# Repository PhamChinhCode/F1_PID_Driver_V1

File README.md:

# F1_PID_Driver_V1

Mạch driver động cơ DC chổi than có điều khiển PID, thiết kế bằng **KiCad**.
Cầu H 4 × N-MOSFET, gate driver IR2184 bootstrap, cách ly quang giữa MCU và phần công suất, vi điều khiển **STM32F103C8** đọc encoder và chạy vòng PID vị trí/tốc độ.

| Mặt trên | Mặt dưới |
|---|---|
|  |  |

## Thông số chính

| Mục | Giá trị |
|---|---|
| Kích thước PCB | 45 × 65 mm, 2 lớp, đồng 1 oz |
| Điện áp động cơ (VM) | ~18 – 35 V (giới hạn bởi L7815 và tụ 50 V) |
| Dòng liên tục thực tế | ~8 – 10 A (giới hạn bởi đồng 1 oz và terminal) |
| MOSFET | 4 × IRFS4321 (TO-263, 150 V) |
| Gate driver | 2 × IR2184 (half-bridge, dead-time nội) |
| Cách ly | HCPL-0630 (2 kênh) cho PWMA/PWMB |
| MCU | STM32F103C8T6, thạch anh ngoài, SWD |
| Logic 3.3 V | AMS1117-3.3, cấp 5 V từ các cổng JST |

## Sơ đồ khối

```
 VM ──F1──┬── Cầu H (Q1–Q4 IRFS4321) ── M+ / M−
          │        ▲            ▲
          │     IR2184 (U1)  IR2184 (U2)
          │        ▲            ▲
          ├─ L7815 → +15VP → AMS1117-5.0 → +5VP
          │        │  PWMA        │ PWMB
          │   ─────┴── HCPL-0630 ─┴─────   (cách ly COM ↔ GND)
          │                ▲
 +5V (JST) → AMS1117-3.3 → STM32F103C8
                           ├─ TIM2 encoder  (PA0/PA1, qua 74x14)
                           ├─ STEP/DIR      (PA6/PA7, qua 74x14)
                           ├─ ADC biến trở  (PA3)
                           ├─ UART1 (PA9/PA10), I2C2 (PB10/PB11)
                           └─ Địa chỉ node  JP1–JP4 (PB12–PB15)
```

## Mapping chân MCU

| Chức năng | Chân | Ngoại vi |
|---|---|---|
| Encoder A/B | PA0 / PA1 | TIM2 encoder mode |
| PULSE (step) | PA6 | TIM3_CH1 |
| DIR | PA7 | GPIO |
| ADIR | PA4 | GPIO |
| Biến trở (analog) | PA3 | ADC1_IN3 |
| PWMA / PWMB | PB6 / PB7 | TIM4_CH1 / CH2 → opto → IR2184 |
| UART | PA9 / PA10 | USART1 |
| I2C | PB10 / PB11 | I2C2 (pull-up 4k7) |
| Địa chỉ node | PB12 – PB15 | Solder jumper xuống GND (ID 0–15) |
| Nạp/debug | PA13 / PA14 | SWD |

> Lưu ý firmware: 74x14 là Schmitt **đảo**, nên tín hiệu DIR/encoder/step bị đảo. Do dùng bootstrap, duty high-side không được giữ 100 % lâu (~95–98 % tối đa).

## Cấu trúc thư mục

| Đường dẫn | Nội dung |
|---|---|
| `F1_PID_Driver_V1.kicad_pro` | Project KiCad |
| `F1_PID_Driver_V1.kicad_sch` | Schematic |
| `F1_PID_Driver_V1.kicad_pcb` | PCB layout |
| `F1_PID_Driver_V1.pdf` | Schematic xuất PDF |
| `bom/ibom.html` | Interactive BOM (mở bằng trình duyệt) |
| `gerber_to_order/` | Gerber cho JLCPCB, PCBWay, Elecrow, FusionPCB… |
| `REVIEW_F1_PID_Driver_V1.md` | Báo cáo review thiết kế (ERC/DRC, lỗi, đề xuất V2) |

## Trạng thái

⚠️ **Bản V1 còn lỗi đã biết** — xem chi tiết trong [REVIEW_F1_PID_Driver_V1.md](REVIEW_F1_PID_Driver_V1.md). Những điểm quan trọng nhất:

- Zener D10 ở ngõ ADC lắp ngược chiều.
- AMS1117-5.0 nhận 15 V (sát/vượt abs-max).
- Thiếu tụ 10 µF ngõ ra LDO, dòng LED opto thấp (R8/R9 330 Ω).
- nSD luôn kéo lên, MCU không tắt được cầu H.
- Gerber trong `gerber_to_order/` (18/06/2026) **cũ hơn** file PCB (04/08/2026) — cần refill zone, chạy DRC và xuất lại trước khi đặt mạch.

Checklist sửa cho V1.1 nằm ở mục 6 của file review.

## Mở dự án

1. Cài [KiCad](https://www.kicad.org/) **10** trở lên (file được lưu bằng KiCad 10, bản cũ hơn không mở được).
2. Mở `F1_PID_Driver_V1.kicad_pro`.
3. Nếu thiếu thư viện/footprint, kiểm tra *Preferences → Manage Symbol/Footprint Libraries*.

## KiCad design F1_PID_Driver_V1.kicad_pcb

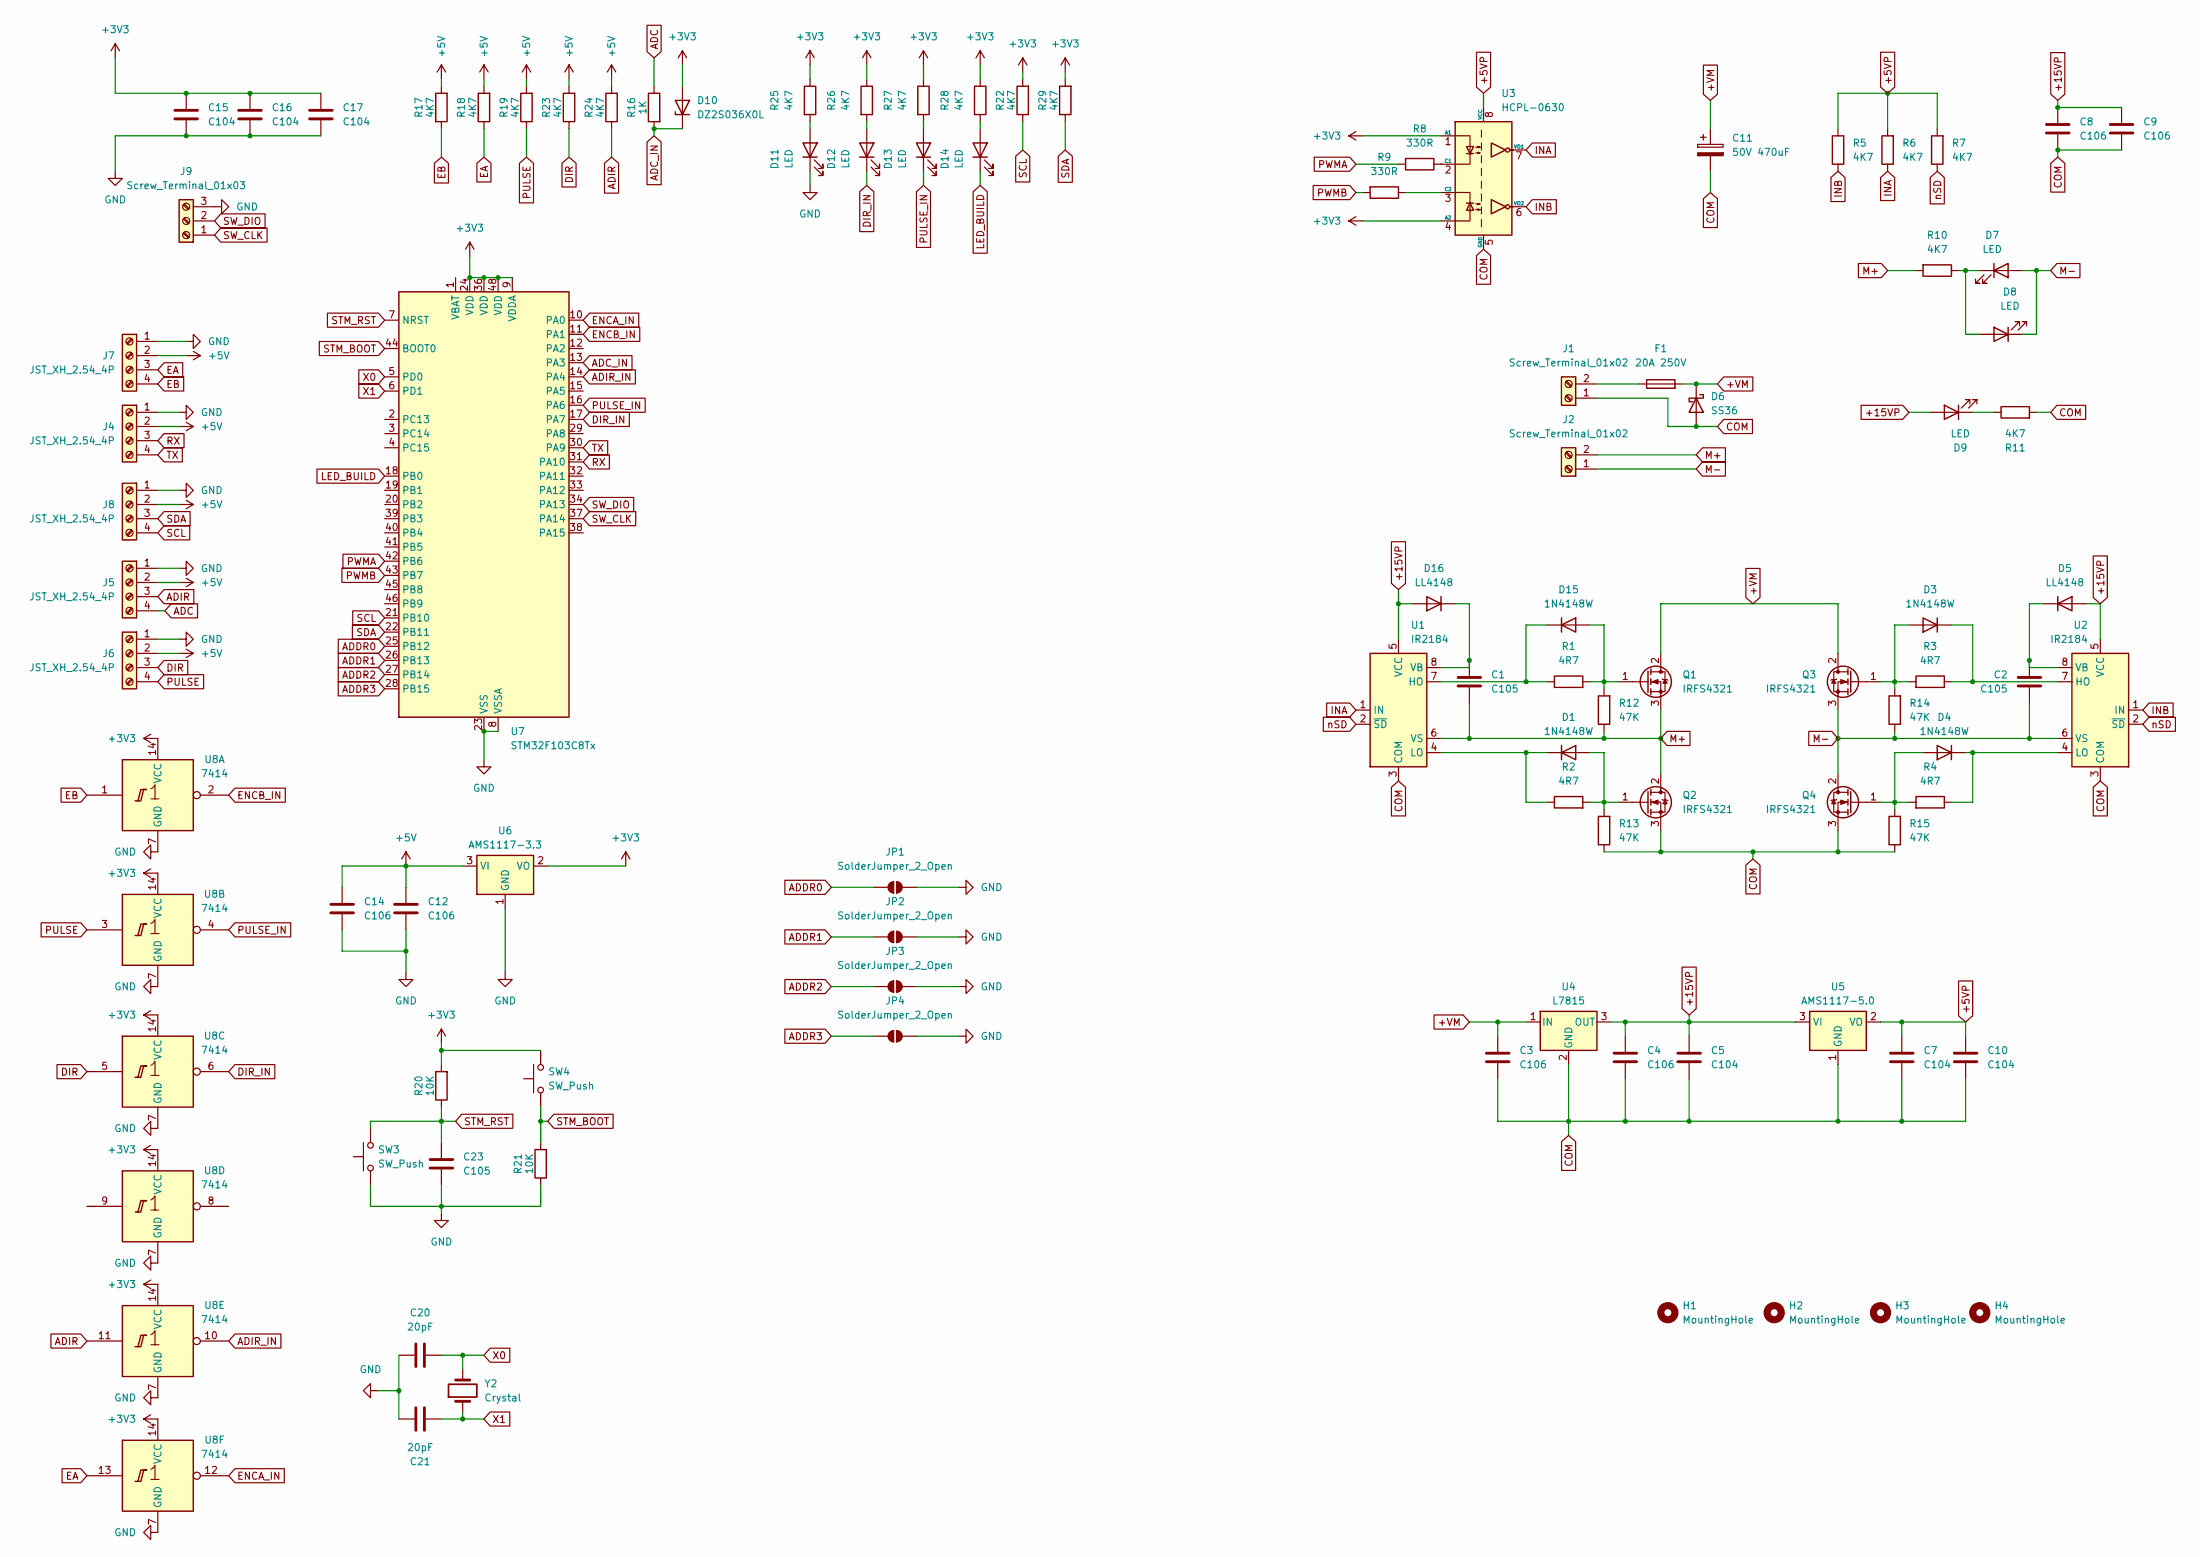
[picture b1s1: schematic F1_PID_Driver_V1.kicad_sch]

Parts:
C1, C2, C23: C105; C_0805_2012Metric
C3, C4, C8, C9: C106; C_1206_3216Metric
C5, C7, C10, C15, C16, C17: C104; C_0805_2012Metric
C11: 50V 470uF; CP_Radial_D10.0mm_P3.50mm
C12, C14: C106; C_0805_2012Metric
C20, C21: 20pF; C_0805_2012Metric
D1, D3, D4, D15: 1N4148W; D_SOD-123
D5, D16: LL4148; D_MiniMELF
D6: SS36; D_SMA
D7, D8, D9, D11, D12, D13, D14: LED; LED_0603_1608Metric
D10: DZ2S036X0L; D_SOD-123F
F1: 20A 250V; Fuseholder_Clip-5x20mm_Keystone_3512_Inline_P23.62x7.27mm_D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
H1, H2, H3, H4: MountingHole; MountingHole_3.2mm_M3_Pad_Via
J1, J2: Screw_Terminal_01x02; TerminalBlock_Phoenix_MKDS-1,5-2-5.08_1x02_P5.08mm_Horizont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
J4, J5, J6, J7, J8: JST_XH_2.54_4P; XH2.54-4P
J9: Screw_Terminal_01x03; JST_PH_B3B-PH-SM4-TB_1x03-1MP_P2.00mm_Vertical
JP1, JP2, JP3, JP4: SolderJumper_2_Open; SolderJumper-2_P1.3mm_Open_RoundedPad1.0x1.5mm
Q1, Q2, Q3, Q4: IRFS4321; TO-263-2
R1, R2, R3, R4: 4R7; R_0805_2012Metric
R5, R6, R7, R10, R11, R17, R18, R19, R22, R23, R24, R25, R26, R27, R28, R29: 4K7; R_0603_1608Metric
R8, R9: 330R; R_0603_1608Metric
R12, R13, R14, R15: 47K; R_0603_1608Metric
R16: 1K; R_0603_1608Metric
R20, R21: 10K; R_0603_1608Metric
SW3, SW4: SW_Push; SW_SPST_TS-1088-xR025
U1, U2: IR2184; SOIC-8_3.9x4.9mm_P1.27mm
U3: HCPL-0630; SOIC-8_3.9x4.9mm_P1.27mm
U4: L7815; TO-252-2
U5: AMS1117-5.0; SOT-223-3_TabPin2
U6: AMS1117-3.3; SOT-223-3_TabPin2
U7: STM32F103C8Tx; LQFP-48_7x7mm_P0.5mm
U8: 7414; SOIC-14_3.9x8.7mm_P1.27mm
Y2: Crystal; Crystal_HC49-4H_Vertical

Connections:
+3V3: C15.1, C16.1, C17.1, D10.2 (A), R20.2, R22.2, R25.1, R26.1, R27.1, R28.1, R29.2, SW4.2, U3.1 (A1), U3.4 (A2), U6.2 (VO), U7.9 (VDDA), U7.24 (VDD), U7.36 (VDD), U7.48 (VDD), U8.14 (VCC)
+5V: C12.1, C14.1, J4.2, J5.2, J6.2, J7.2, J8.2, R17.2, R18.2, R19.2, R23.2, R24.2, U6.3 (VI)
+5VP: C7.1, C10.1, R5.2, R6.2, R7.2, U3.8 (VCC), U5.2 (VO)
+15VP: C4.1, C5.1, C8.1, C9.1, D5.2 (A), D9.2 (A), D16.2 (A), U1.5 (VCC), U2.5 (VCC), U4.3 (OUT), U5.3 (VI)
+VM: C3.1, C11.1, D6.1 (K), F1.2, Q1.2 (D), Q3.2 (D), U4.1 (IN)
ADC: J5.4, R16.1
ADC_IN: D10.1 (K), R16.2, U7.13 (PA3)
ADDR0: JP1.1 (A), U7.25 (PB12)
ADDR1: JP2.1 (A), U7.26 (PB13)
ADDR2: JP3.1 (A), U7.27 (PB14)
ADDR3: JP4.1 (A), U7.28 (PB15)
ADIR: J5.3, R24.1, U8.11
ADIR_IN: U7.14 (PA4), U8.10
COM: C3.2, C4.2, C5.2, C7.2, C8.2, C9.2, C10.2, C11.2, D6.2 (A), J1.1, Q2.3 (S), Q4.3 (S), R11.2, R13.1, R15.1, U1.3 (COM), U2.3 (COM), U3.5 (GND), U4.2 (GND), U5.1 (GND)
DIR: J6.3, R23.1, U8.5
DIR_IN: D12.1 (K), U7.17 (PA7), U8.6
EA: J7.3, R18.1, U8.13
EB: J7.4, R17.1, U8.1
ENCA_IN: U7.10 (PA0), U8.12
ENCB_IN: U7.11 (PA1), U8.2
GND: C12.2, C14.2, C15.2, C16.2, C17.2, C20.1, C21.1, C23.2, D11.1 (K), J4.1, J5.1, J6.1, J7.1, J8.1, J9.3, JP1.2 (B), JP2.2 (B), JP3.2 (B), JP4.2 (B), R21.1, SW3.1, U6.1 (GND), U7.8 (VSSA), U7.23 (VSS), U7.35 (VSS), U7.47 (VSS), U8.7 (GND)
INA: R6.1, U1.1 (IN), U3.7 (VO1)
INB: R5.1, U2.1 (IN), U3.6 (VO2)
LED_BUILD: D14.1 (K), U7.18 (PB0)
M+: C1.2, J2.2, Q1.3 (S), Q2.2 (D), R10.2, R12.1, U1.6 (VS)
M-: C2.2, D7.2 (A), D8.1 (K), J2.1, Q3.3 (S), Q4.2 (D), R14.1, U2.6 (VS)
unnamed: D1.2 (A), Q2.1 (G), R2.2, R13.2
unnamed: D1.1 (K), R2.1, U1.4 (LO)
unnamed: D3.2 (A), Q3.1 (G), R3.2, R14.2
unnamed: D3.1 (K), R3.1, U2.7 (HO)
unnamed: D4.2 (A), Q4.1 (G), R4.2, R15.2
unnamed: D4.1 (K), R4.1, U2.4 (LO)
unnamed: C2.1, D5.1 (K), U2.8 (VB)
unnamed: D7.1 (K), D8.2 (A), R10.1
unnamed: D9.1 (K), R11.1
unnamed: D11.2 (A), R25.2
unnamed: D12.2 (A), R26.2
unnamed: D13.2 (A), R27.2
unnamed: D14.2 (A), R28.2
unnamed: D15.2 (A), Q1.1 (G), R1.2, R12.2
unnamed: D15.1 (K), R1.1, U1.7 (HO)
unnamed: C1.1, D16.1 (K), U1.8 (VB)
unnamed: F1.1, J1.2
unnamed: R8.1, U3.2 (C1)
unnamed: R9.1, U3.3 (C2)
PULSE: J6.4, R19.1, U8.3
PULSE_IN: D13.1 (K), U7.16 (PA6), U8.4
PWMA: R8.2, U7.42 (PB6)
PWMB: R9.2, U7.43 (PB7)
RX: J4.3, U7.31 (PA10)
SCL: J8.4, R22.1, U7.21 (PB10)
SDA: J8.3, R29.1, U7.22 (PB11)
STM_BOOT: R21.2, SW4.1, U7.44 (BOOT0)
STM_RST: C23.1, R20.1, SW3.2, U7.7 (NRST)
SW_CLK: J9.1, U7.37 (PA14)
SW_DIO: J9.2, U7.34 (PA13)
TX: J4.4, U7.30 (PA9)
X0: C20.2, U7.5 (PD0), Y2.2
X1: C21.2, U7.6 (PD1), Y2.1
nSD: R7.1, U1.2 (~SD), U2.2 (~SD)

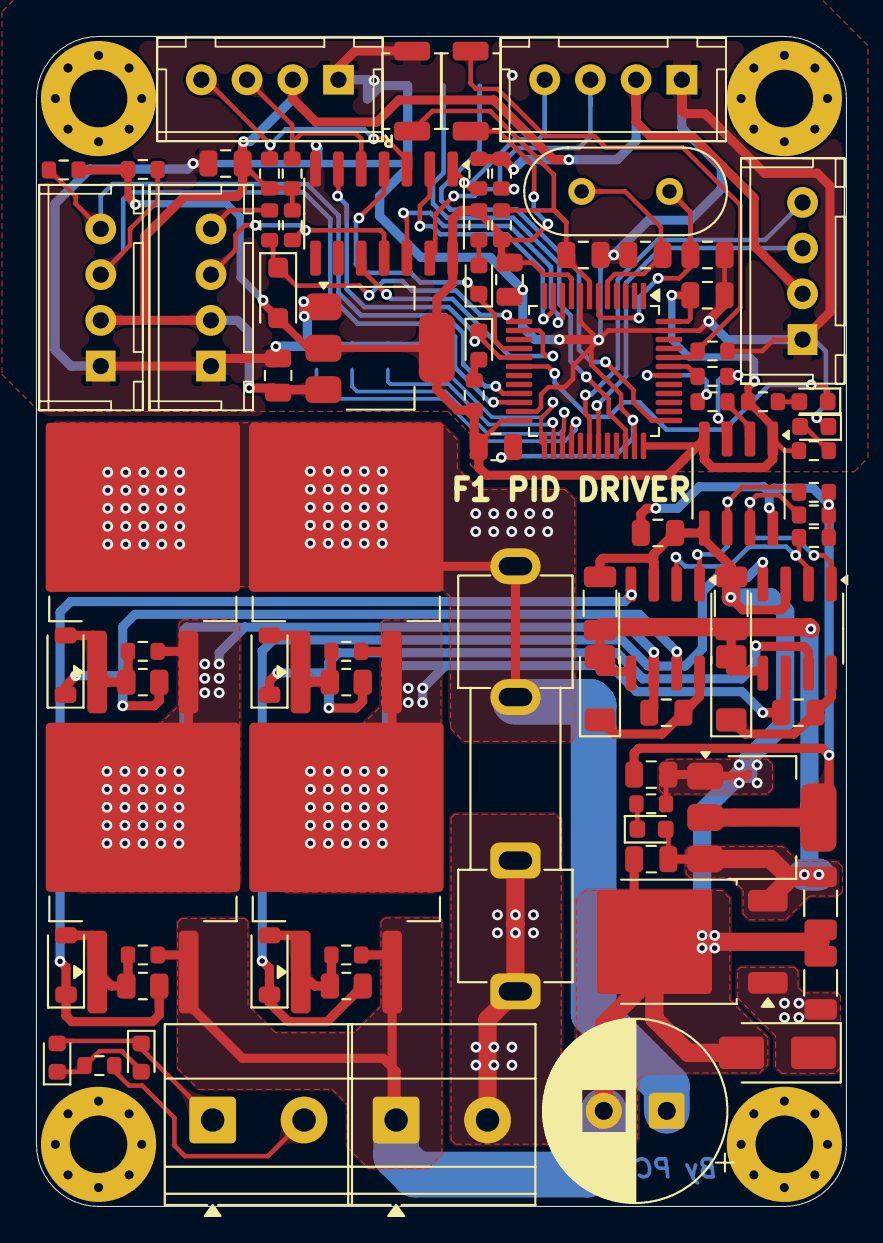
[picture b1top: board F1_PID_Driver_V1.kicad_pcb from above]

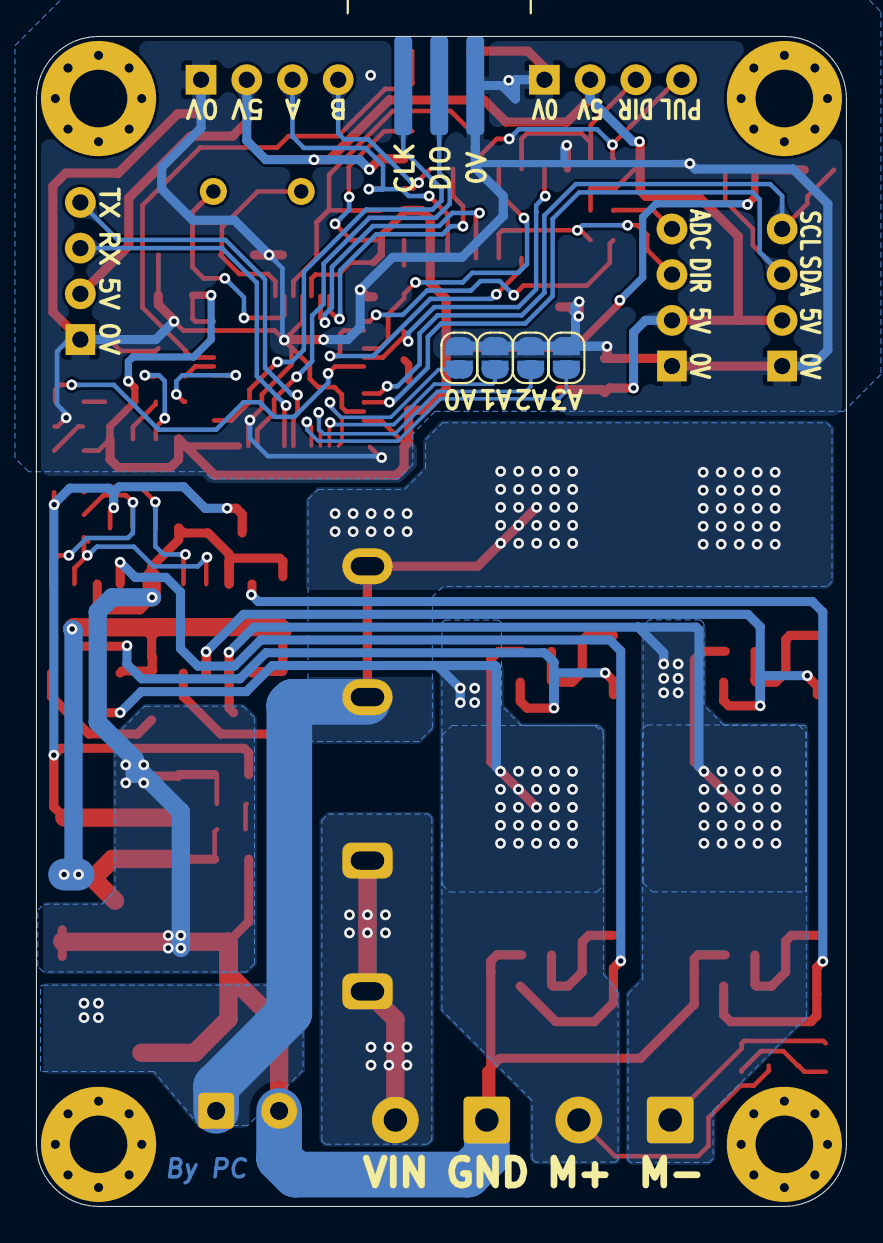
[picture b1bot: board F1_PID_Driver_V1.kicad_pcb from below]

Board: 2 copper layers, 45.0 x 65.0 mm, 94 parts (5 on the bottom side), 60 nets.
